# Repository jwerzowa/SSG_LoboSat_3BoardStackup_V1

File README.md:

# LOBOSAT 3-Board PCB Stackup V1

KiCad PCB designs for the LOBOSAT CubeSat, developed as part of UNM's satellite club (LOBOSAT/SSG).
Reach out to Julien Werzowa for any questions. 

## Board Overview

Boards:   

| `Feather_IMU_Board - Telemetry` : Adafruit Feather M0 RFM95 + Sparkfun ICM-20948 9-DOF IMU |  
| `Raspberry_PI_Board - Videography` : Raspberry Pi Zero 2W compute board use for Videography |  
| `Lightracker_Battery_Board - Power & GPS` : LightTracker + DFR1015 buck converter (7.4V → 5V) |     

## Power Architecture

7.4V LiPo → DFR1015 buck converter → 5V rail distributed across all three boards via 2×8 dual-row headers.

## Tools

- KiCad 9
- Fabrication: JCLPCB

## Status

V1 — initial commit. Work in progress.

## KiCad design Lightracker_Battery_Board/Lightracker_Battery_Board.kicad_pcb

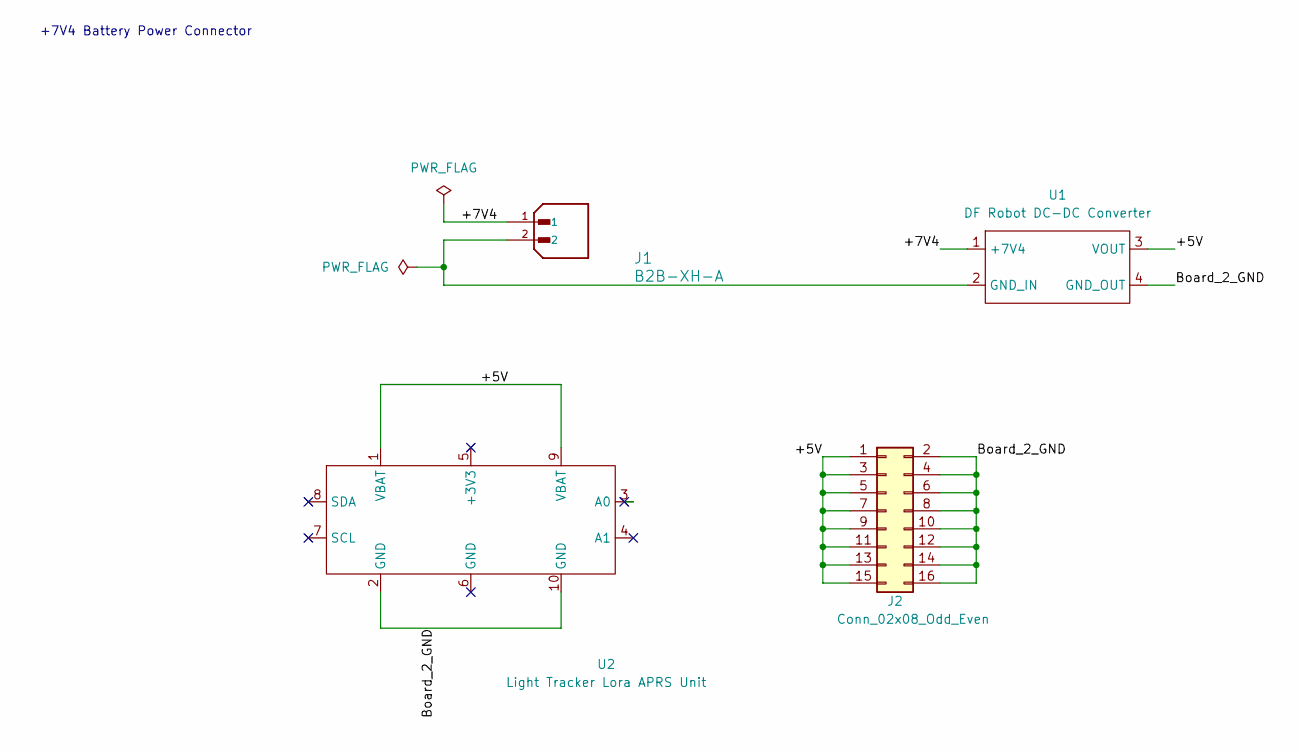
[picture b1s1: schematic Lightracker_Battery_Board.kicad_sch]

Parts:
J1: B2B-XH-A; JST_XH_B2B-XH-A_1x02_P2.50mm_Vertical; PARTREV N/A
J2: Conn_02x08_Odd_Even; PinHeader_2x08_P2.54mm_Vertical
U1: DF Robot DC-DC Converter; Sat_Club_Buck_Converter
U2: Light Tracker Lora APRS Unit; Light_Tracker

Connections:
/+5V: J2.1, J2.3, J2.5, J2.7, J2.9, J2.11, J2.13, J2.15, U1.3 (VOUT), U2.1 (VBAT), U2.9 (VBAT)
/+7V4: J1.1, U1.1 (+7V4)
/Board_2_GND: J2.2, J2.4, J2.6, J2.8, J2.10, J2.12, J2.14, J2.16, U1.4 (GND_OUT), U2.2 (GND), U2.10 (GND)
unnamed: J1.2, U1.2 (GND_IN)

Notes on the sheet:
+7V4 Battery Power Connector

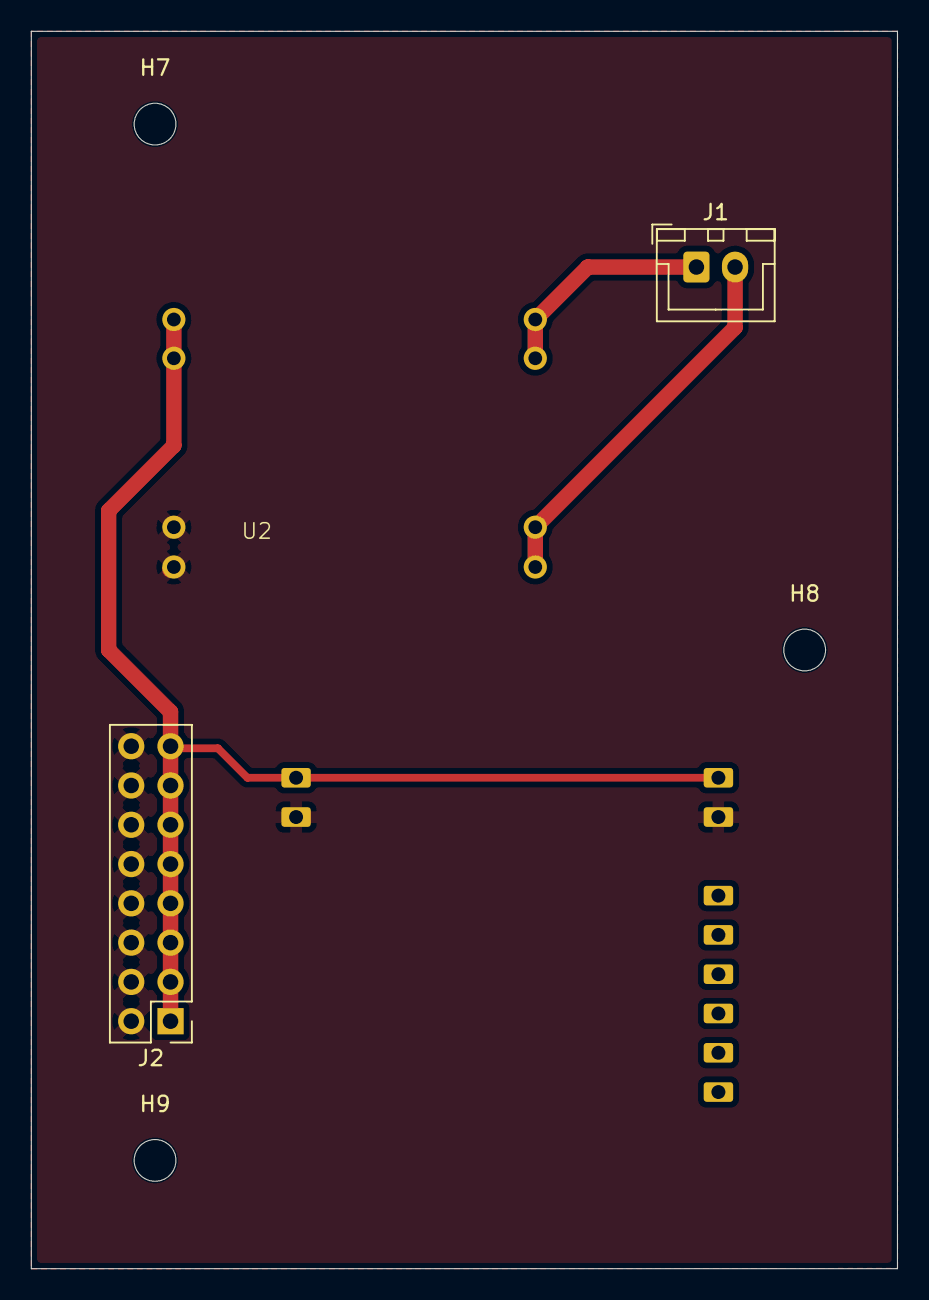
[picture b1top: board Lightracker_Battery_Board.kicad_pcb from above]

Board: 2 copper layers, 56.0 x 80.0 mm, 7 parts (1 on the bottom side), 4 nets.

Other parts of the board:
H7, H8, H9: MountingHole_2.7mm_M2.5

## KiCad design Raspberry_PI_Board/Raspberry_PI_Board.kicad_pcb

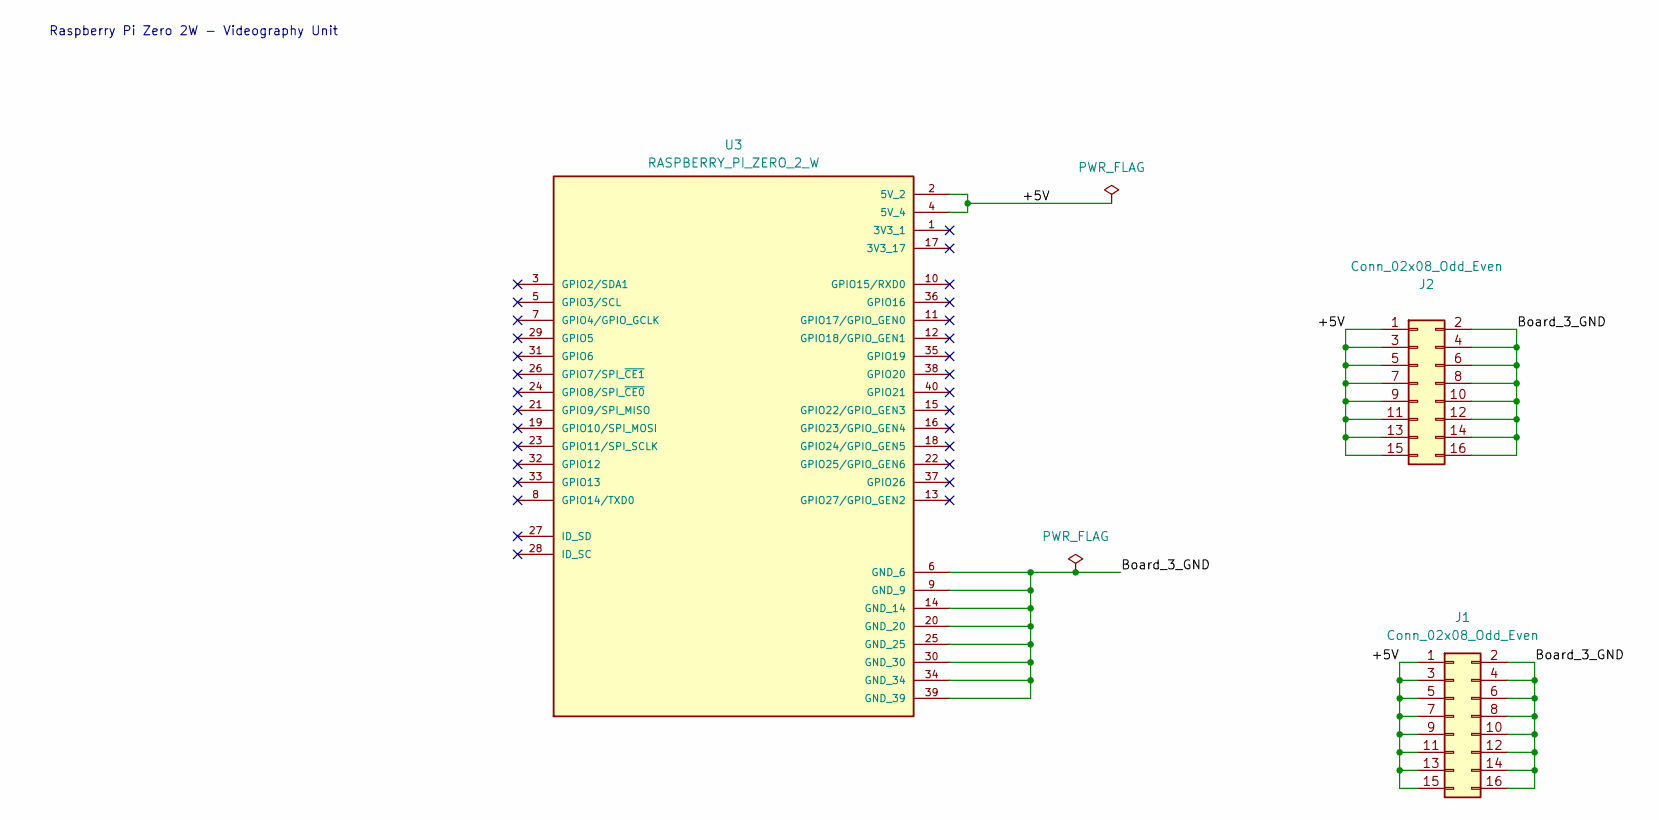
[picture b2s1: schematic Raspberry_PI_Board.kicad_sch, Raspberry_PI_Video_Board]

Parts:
J1, J2: Conn_02x08_Odd_Even; PinHeader_2x08_P2.54mm_Vertical
U3: RASPBERRY_PI_ZERO_2_W; Raspberry_Pi_Zero_Socketed_THT_FaceDown_MountingHoles; PARTREV April 2024

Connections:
/+5V: J1.1, J1.3, J1.5, J1.7, J1.9, J1.11, J1.13, J1.15, J2.1, J2.3, J2.5, J2.7, J2.9, J2.11, J2.13, J2.15, U3.2 (5V_2), U3.4 (5V_4)
/Board_3_GND: J1.2, J1.4, J1.6, J1.8, J1.10, J1.12, J1.14, J1.16, J2.2, J2.4, J2.6, J2.8, J2.10, J2.12, J2.14, J2.16, U3.6 (GND_6), U3.9 (GND_9), U3.14 (GND_14), U3.20 (GND_20), U3.25 (GND_25), U3.30 (GND_30), U3.34 (GND_34), U3.39 (GND_39)

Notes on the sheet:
Raspberry Pi Zero 2W - Videography Unit

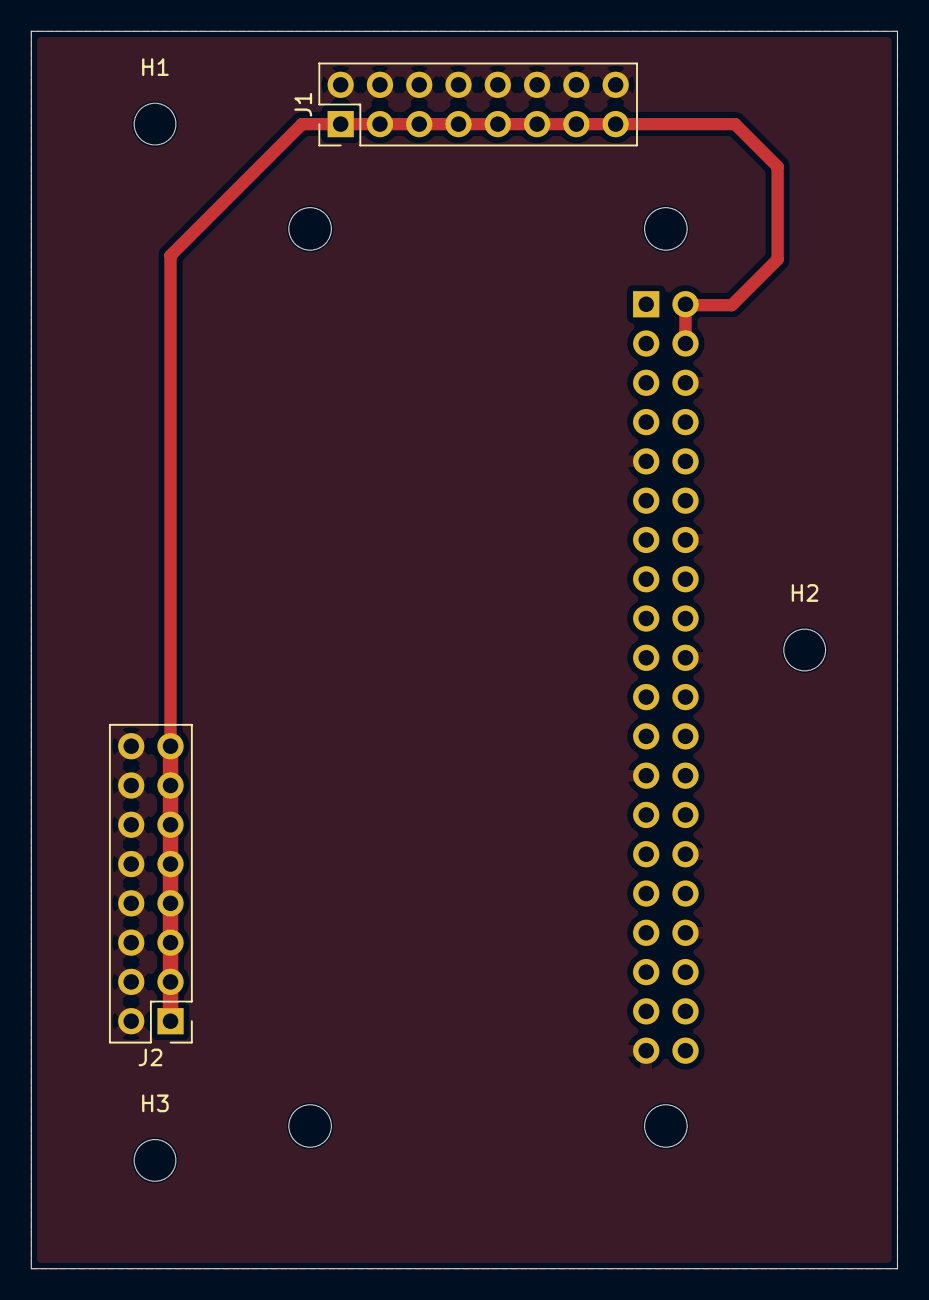
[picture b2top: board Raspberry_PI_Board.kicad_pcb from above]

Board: 2 copper layers, 56.0 x 80.0 mm, 6 parts (1 on the bottom side), 2 nets.

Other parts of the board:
H1, H2, H3: MountingHole_2.7mm_M2.5

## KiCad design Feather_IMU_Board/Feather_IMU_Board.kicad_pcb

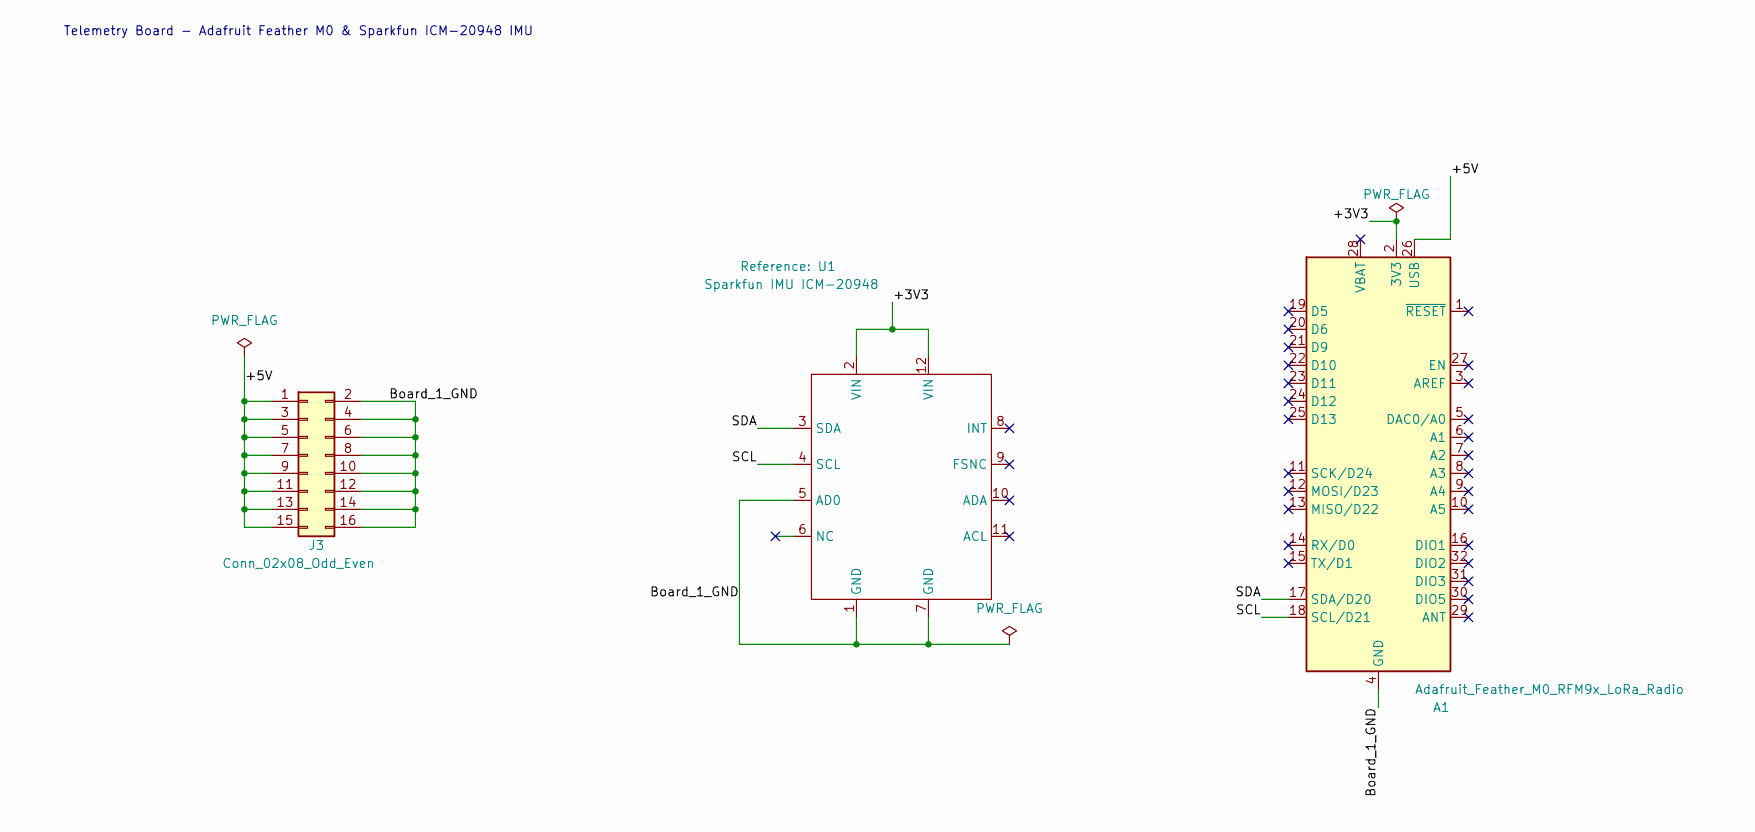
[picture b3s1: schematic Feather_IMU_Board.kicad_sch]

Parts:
A1: Adafruit_Feather_M0_RFM9x_LoRa_Radio; Adafruit_Feather_M0_RFM
J3: Conn_02x08_Odd_Even; PinHeader_2x08_P2.54mm_Vertical
U1: Sparkfun IMU ICM-20948; SparkFun_ICM20948_Breakout_2x06_23mm

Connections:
/+3V3: A1.2 (3V3), U1.2 (VIN), U1.12 (VIN)
/+5V: A1.26 (USB), J3.1, J3.3, J3.5, J3.7, J3.9, J3.11, J3.13, J3.15
/Board_1_GND: A1.4 (GND), J3.2, J3.4, J3.6, J3.8, J3.10, J3.12, J3.14, J3.16, U1.1 (GND), U1.5 (AD0), U1.7 (GND)
/SCL: A1.18 (SCL/D21), U1.4 (SCL)
/SDA: A1.17 (SDA/D20), U1.3 (SDA)

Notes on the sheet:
Telemetry Board - Adafruit Feather M0 & Sparkfun ICM-20948 IMU

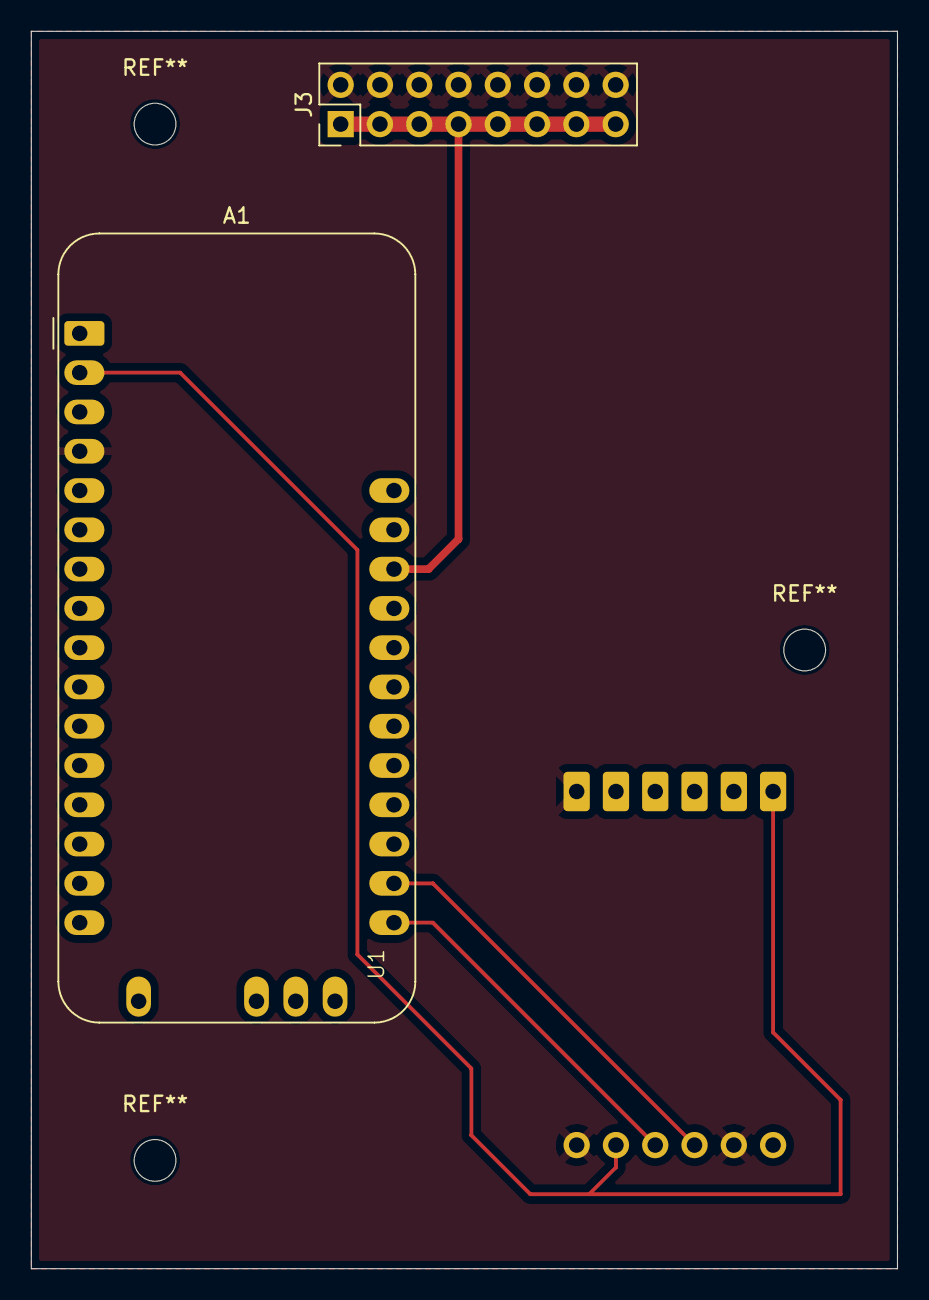
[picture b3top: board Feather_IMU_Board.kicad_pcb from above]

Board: 2 copper layers, 56.0 x 80.0 mm, 3 parts (0 on the bottom side), 5 nets.

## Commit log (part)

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2026-06-25 Create README.md for LOBOSAT 3-Board PCB Stackup
    Added initial README.md with project overview and details.
2026-06-25 Fix formatting in Board Overview section of README
2026-06-25 Update KiCad version and fabrication source
    Updated KiCad version and fabrication source in README.
2026-06-25 Revise board overview section in README
    Updated board descriptions to use table format for clarity.
2026-06-25 Fix formatting in README for board descriptions
